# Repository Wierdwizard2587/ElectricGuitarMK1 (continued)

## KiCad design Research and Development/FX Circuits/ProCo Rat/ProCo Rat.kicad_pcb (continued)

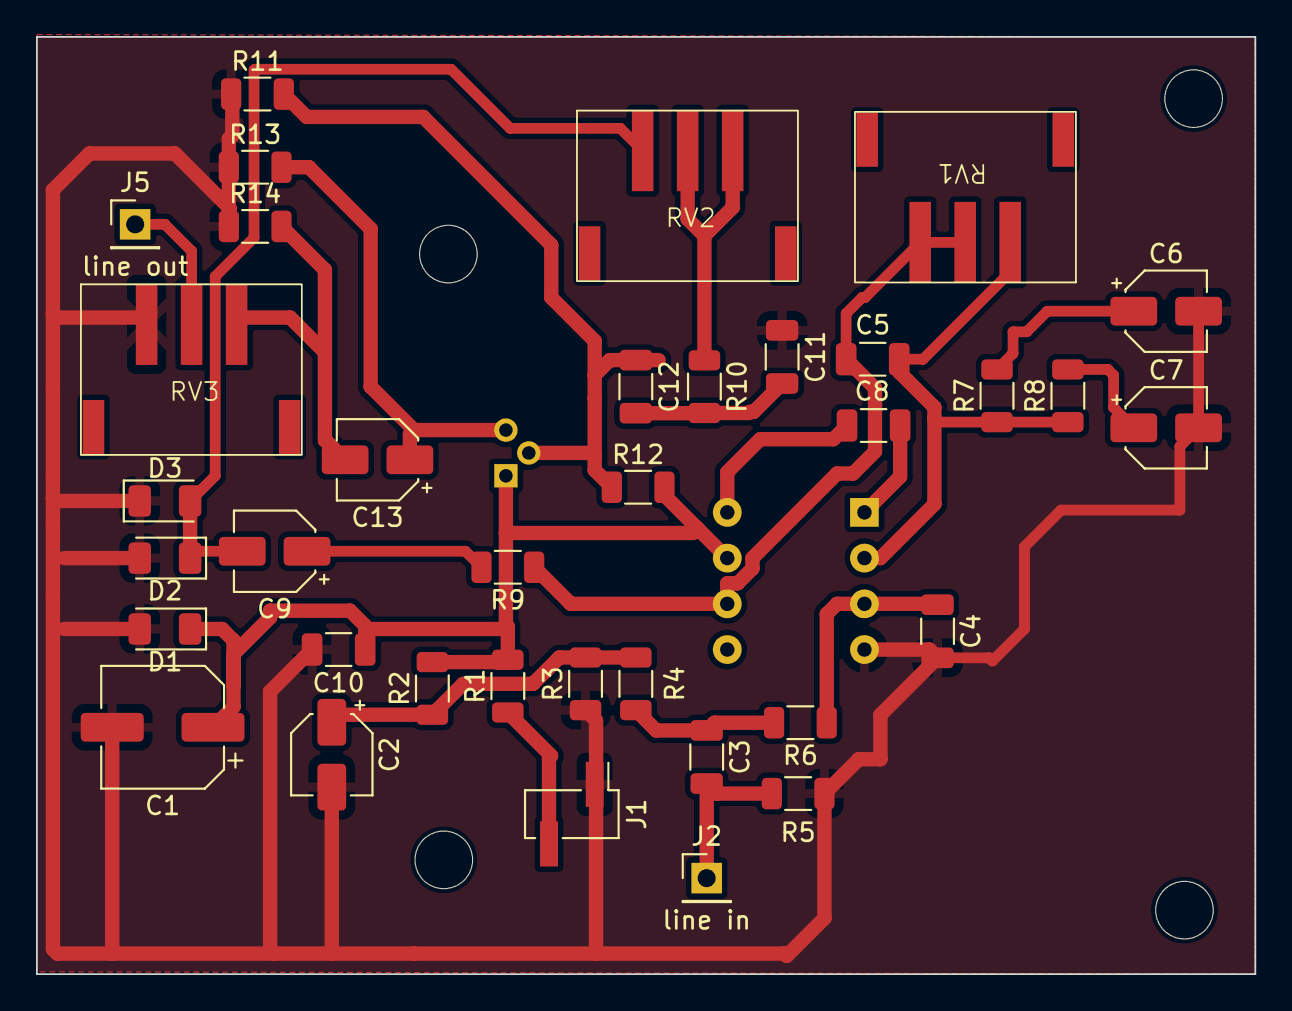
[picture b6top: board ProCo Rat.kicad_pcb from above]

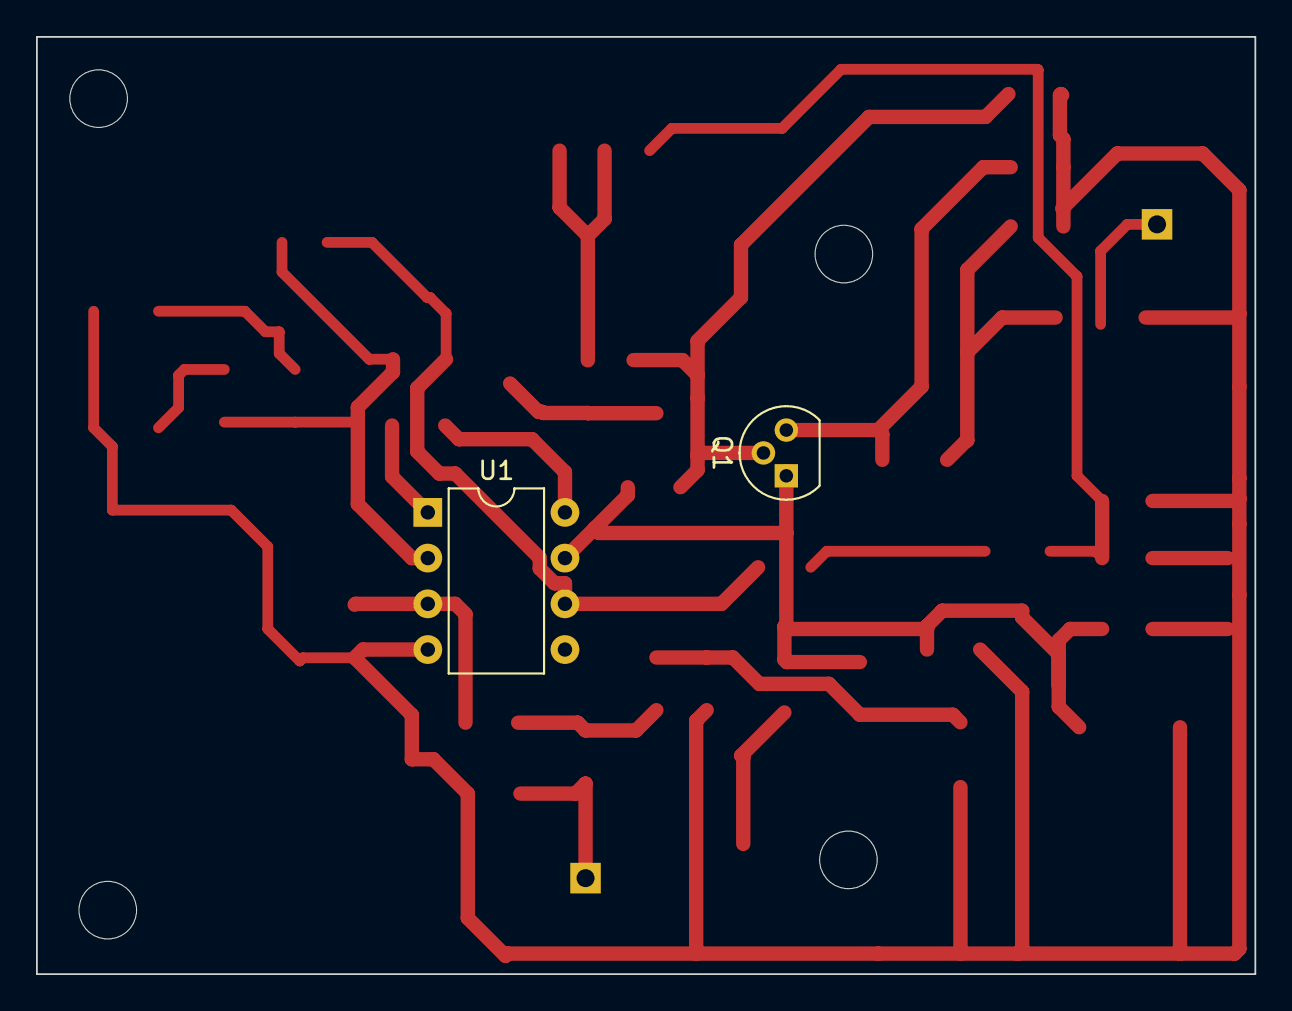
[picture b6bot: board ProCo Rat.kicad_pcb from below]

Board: 2 copper layers, 67.7 x 52.1 mm, 38 parts (2 on the bottom side), 21 nets.

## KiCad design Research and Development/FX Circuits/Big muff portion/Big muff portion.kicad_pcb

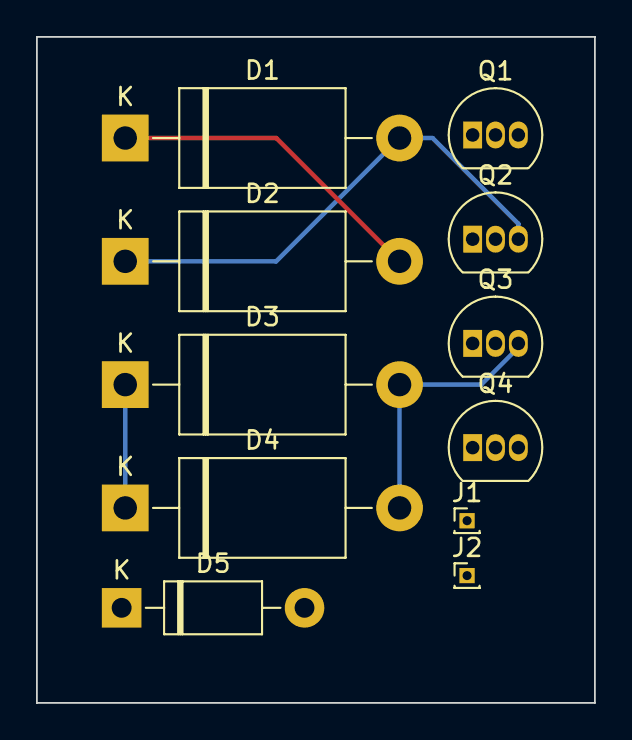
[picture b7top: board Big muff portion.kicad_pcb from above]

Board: 2 copper layers, 31.0 x 37.0 mm, 11 parts (0 on the bottom side), 4 nets.

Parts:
D1, D2, D3, D4: 1N62xxA; D_DO-201AE_P15.24mm_Horizontal
D5: 1N4001; D_DO-41_SOD81_P10.16mm_Horizontal
J1: IN; PinHeader_1x01_P1.00mm_Vertical
J2: OUT; PinHeader_1x01_P1.00mm_Vertical
Q1, Q2, Q3, Q4: TO-92_Inline

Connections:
unnamed: D1.1 (A1), D2.2 (A2)
unnamed: D1.2 (A2), D2.1 (A1), Q2.3 (C)
unnamed: D3.1 (A1), D4.1 (A1)
unnamed: D3.2 (A2), D4.2 (A2), Q3.3 (C)

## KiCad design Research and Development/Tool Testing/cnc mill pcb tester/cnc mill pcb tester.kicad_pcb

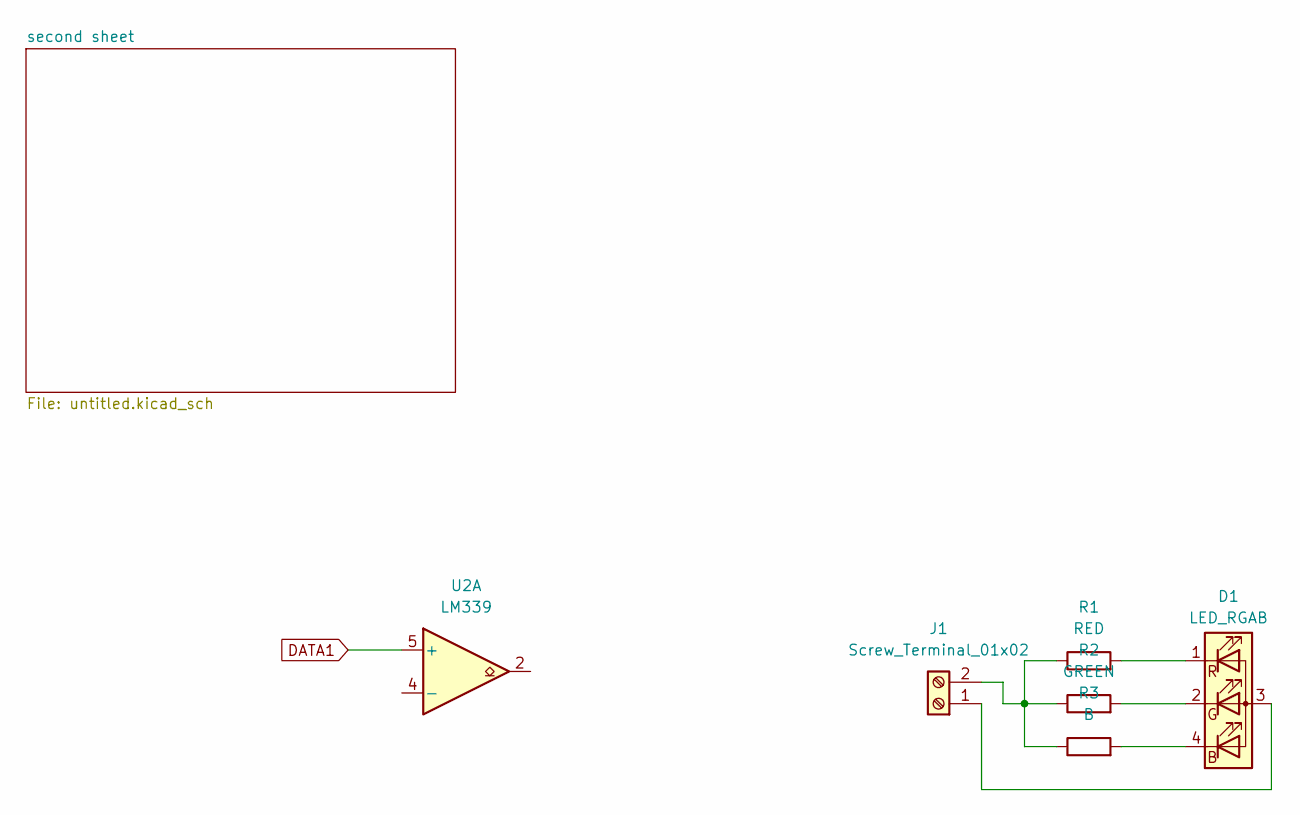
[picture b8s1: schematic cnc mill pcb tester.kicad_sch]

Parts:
D1: LED_RGAB; LED_D5.0mm-4_RGB
J1: Screw_Terminal_01x02; TerminalBlock_Altech_AK300-2_P5.00mm
R1: RED; R_Axial_DIN0207_L6.3mm_D2.5mm_P10.16mm_Horizontal
R2: GREEN; R_Axial_DIN0207_L6.3mm_D2.5mm_P10.16mm_Horizontal
R3: B; R_Axial_DIN0207_L6.3mm_D2.5mm_P10.16mm_Horizontal
U2: LM339; SOIC-14_3.9x8.7mm_P1.27mm

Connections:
DATA1: U2.5 (+); also elsewhere on the board
unnamed: D1.3 (A), J1.1
unnamed: D1.4 (BK), R3.2
unnamed: D1.2 (GK), R2.2
unnamed: D1.1 (RK), R1.2
unnamed: J1.2, R1.1, R2.1, R3.1

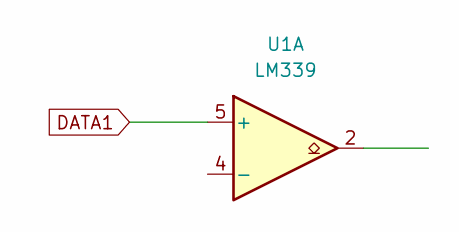
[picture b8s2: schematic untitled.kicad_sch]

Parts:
U1: LM339; SOIC-14_3.9x8.7mm_P1.27mm

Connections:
DATA1: U1.5 (+); also elsewhere on the board

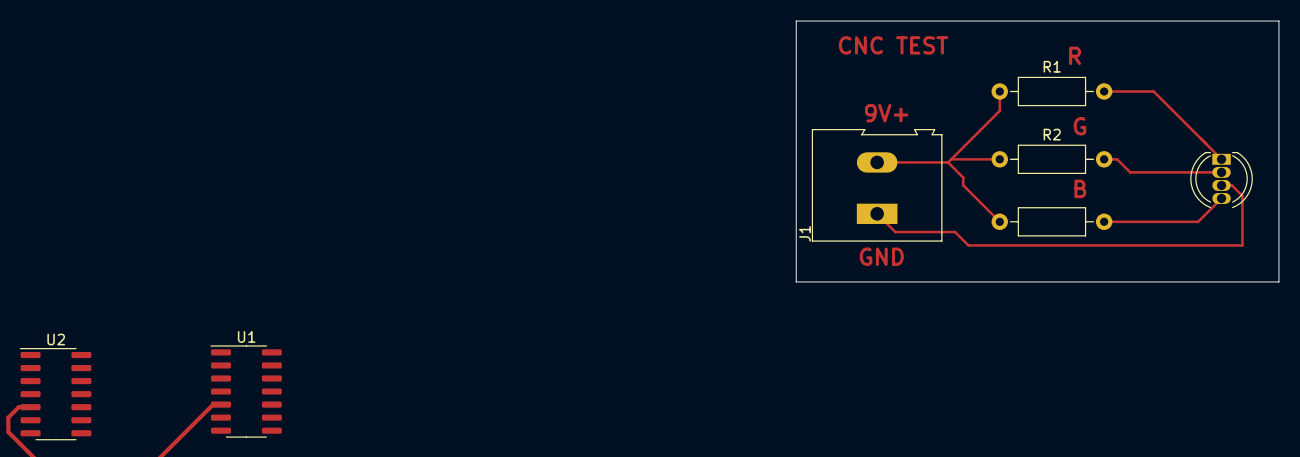
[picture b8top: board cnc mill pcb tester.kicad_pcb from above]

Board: 2 copper layers, 47.0 x 25.4 mm, 7 parts (0 on the bottom side), 6 nets.

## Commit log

2023-11-14 Test to commit with folder
2024-06-01 Added pre existing ki kad files
2024-06-03 Finalised BMS schematic befeore testing PCB
    is rough design without considering guitar dimension, little EMI considerations. not all concepts in design have been ensured to work properly. will test each sections viability before testing entire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
    first design with the batterys and the circuit on the same board. initially had the idea of a 3d printed holder for the cells and a board on top.
    then 3 layers of single sided pcbs triple deckered with smd battery mounts. finally to this style.
    although the board is larger in width and length, the height is reduced which should permit a slot in battery design for the guitar rather than a large module with a rail on the side of the guitar fo
2024-06-03 transfering from pc to git
2024-06-03 Transfered more scripts, models, pcb files and docs over from PC
2024-06-05 updated PCB and tidied up schematic BMS
    Not final version. will revamp the charger in with 5 pins, 1 power for charging and powering load.
    so charging section will be re implemented.
    more 3d models added to board, bms etc
2024-06-09 updated bms schem and pcb and added initial schem for charger
    fixed charging switch logic for bms board, updated jst conns and now instead uses the supply v as the sw V+ to turn off the mosfet to then charge. should work considering it takes 100ns ~ to switch. 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
    created the initial schematic from my notes for a charger that works in respect to the BMS board, is in the same cad file but different sheet to bms and is a seperate pcb.
    still need to finalise the caps and also determine pcb via diameters with what i have available and the size requirements. will follow the suggestion for via size from kicad foru
2024-06-09 updated trace constraints and updated existing traces on board to suit their current
2024-06-17 updated bms schem
    fixed polarity on batteries, updated jst conns to XH, created footprints for them, tidied up and shrunk the board size, changed from using the ds18d20b to a 10k ntc thermistor for temperature control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
2024-07-18 redone bms board and added test bms schem and board to test functionality without the batteries
    added:
    - bms test schem and layout
    - updated bms
    - testing of quad rotary encoder breakout board
    - testing of teensy audio board
    - combining the encoders and audio board in 1 circuit with limited control of chorus fx with encoders
2024-07-24 V1 of interface program
    added home button, quad rotary encoders, oled screen and audio in infrastructure with basic code for loading screen, landing page with screen animations and toggling/ manipulating chorus, reverb and 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
    mix of serial print and oled screen for information for now. very messy code
    unrevised as of yet. will be utilising librarys to simplify source code
2024-07-24 failed custom library testing
    pushing to git for records and calling back for use one library usage is tackled properly
2024-07-25 revised interface Main code
    made the fx functions to be more object oriented.
    added flange fx
    finished base screen layout for fx's
    will next revise screen layout for fx's to be more efficient
2024-07-25 revised mainV1 interface 2.0
    revised fx screen layout. touched up some user experience parts such as remembering the last fx the user was on before returning home and highlighting the landing page cursor on loading. tidied up co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
    next revisions will be for the landing page to reuse some functions designed for the fx page for reading the encoders.
    next section of functionality to be added next will be the audio page to control the master volume, gain and switching of output between headphones and line out for speaker as base functions of secti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
2024-07-29 upgraded interface software
    improved controls of audio pages. streamlined more page processes for less code
    added SD card utilisation which reads a txt file on the card and sets all initial variables there stored values. continuing to work through updating values in the txt file and experementing with the 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
    currently the delay fx updates the file every time the delay time is increased which causes a delay (pun not intended) in the changing of the value.
    the other 3 FX use a still not working method that stores up to 3 different variables changed and their new values. if its changed again the same variable will be changed. once 3 is reached each of t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
2024-08-04 Updated SD Card Usage and designed PCB for AFPI Device
    Created a new method that reads all existing variables and updates all existing variables instead of only the ones that are updated to update all variables in the file. currently this is only actione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
    the next thing to implement for the sd card is to create a temporary file to store the variables while writing it so that it can prevent corruption causing a loss of data so that there will always be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
    the AFPI Device V1.0 PCB is introduced as well to incorperate all the hardware into one circu
2024-08-05 completed AFPI V1.1 Design
    Finished Design and ordered AFPI V1.1 Board
    tided up interface section on repository
2024-08-15 Completed First Revision of AFPI design and Assembly
    Finished the initial design and g code generation of the top and bottom plates of the AFPI as well as the central enclosure. couldnt make gcode to fillet the exterior and interior edges as seen on th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
    Currently all packages for the AFPI have arrived and ive already produced the Top and Bottom plates. i took 2 takes fo
2024-08-25 restarted AFPI code development
    now with the device built, most of the features need their code written to test.
    have commented all serial comms to work without the connection and added the ability to take the line in input and mix it with a aux input, however the aux input audio quality is wierdly scrambled an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
    have begun testing an audio output switch to switch between the speaker amp, headphone out or aux out, and while the headphone and i believe the aux out will mute and unmute when not in use, the spea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
    testing the circuit the op amp recieves the 9 volts and when turning the gain and volume trim pots to the
2024-08-26 Solved Speaker Issue
    After reviewing the pcb layout and the schematic, and reviewing each component, i noticed that the pin outs on the symbol for the MPF102 on the schem didnt number the pins correctly to their function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
    While i did check for the different pinouts as i was aware they vary from models, with the symbol
2024-08-27 First round of modularisation of interface code.
    successfully incorperated the use of librarys in program to sperate different sections of the code, readability and will inevitably efficiency as the code was too long and complicated for one page. f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
    for now there is still an over use of global variables and when each section is fully and properly seperated i can then start encapsulating the sections in classes etc. All in all good progress con
2024-08-28 second round of improving current interface code
    i have created all libraries neccesary for seperating sections of the program into their respective sections, for each of the page sections aswell as the peripherals code for initialising and sending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
2024-08-28 incorperation of new features to interface code
    added the following new features:
    - able to manipulate the OLED contrast to set the brightness of the screen in the settings section, currently between 0-255 in steps of 5 but will make it smaller in future for easier use
    - added screen saver functionality to count 10 seconds and if 10 seconds is reached, the screen is cleared and the program waits in pergatory for a interaction with the buttons/encoders. if one is pr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
2024-08-30 added volume and gain control to specific outputs depending on chosen output
    while still janky and variables arent very linear for the speaker and aux, i can control the vol and gain on the specific output chosen now, rather than just the headphone output, now whats left to f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
    in the future the variables shown to the user will need to be more uniform as the vol for the speaker cuts out at 0.65 so that needs to be made 0 and 1.0 needs t
2024-08-31 Completed Audio Output Control and updated SD card storage system
    Fixed all known bugs in audio output section, while the code for determining the current audio output and directing variable setting/carrying out gain/volume update is somewhat improper and isnt an e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
    the sd card variables were also updated for not only the audio output section but also any other new features that hadnt had their variables added. this was done by also using AI to create for me a p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
2024-09-03 introduced RGB control
    I soldered together 6 ws2812 LED's and fixed up the rgb connector wiring so that it wasnt in the way of the usb programming cable. i then programmed the interval timer to check when 20ms has passed d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
    the initialisation of the leds was set up and incorperated as well as the neccesary variables added to the sd card storage system. from there i added a simple on off of a basic flowing effect that
2024-09-05 completed min specs for lighting and Low power mode
    The lighting code has been completed to the point where the only things to add is more lighting modes. the 2nd light mode atm will be turned into another colour option as its a slower rainbow than th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
    the low power mode feature has also been incorperated and for now it reduces the led brightness to max out at 50 instead of 255, the same goes for the oled contrast. the screen saver timer is
2024-09-08 Completed Lighting Board and 3d Model of lighting assembly
    After finishing the minimum requirement code for the RGB lighting to function i have now designed the 2 PCBs that will house the LEDS as well as designed the mounting of these board for to the guitar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
    the PCBS are numbered 1 and 2, 1 being placed between the neck and middle single coil pickups and 2 being mounted between the middle and bridge pickups. board one is the main PCB as the output from t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
2024-09-18 designed and awaiting testing of Battery Circuit Design and Enclosure functionality
    i have fully simplified the batterys circuitry down to reduce the amount of time spent on the battery to be a little as possible to ensure the minimum requirements are met and that i ensure i meet th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
2024-09-23 updated battery enclosure design to v1.1
    after printing and testing the battery design i found multiple flaws in the design:
    - the pockets for the spring bolt, handle insert to bolt and bolt hole on top plate were too small and needed to be widened with files and a dremel.
    - the sleeve wasnt made big enough for a smooth slide and had to be 'broken in' and would get stuck and had to hammer out the battery.
    - the battery wasnt easy to remove as there was no proper grip to pull it out with.
    to fix these issues i resized the sleeve 0.7mm bigger on the sides and 0.5mm on the top for a smoother slide and the bolt was redesigned to more easily fit the handle into. 2 holes on either side of 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
2025-05-16 Belated Commit of final Files after completed
    I actually completed this on the 31/12/2025 however due to busy new year it was forgotten to commit after the Guitar was completed. Very happy with how it turned out and have many future ideas to inc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
2025-05-16 Photos Committed
    All photos related to the planning, research, design and assembly of the guitar Mk1
2025-05-18 extra photo
2025-06-23 created Documentation File
2025-06-23 put readme file back in correct location
2025-06-23 Update README.md
    added contents page
2025-07-03 Tidy up Repo
